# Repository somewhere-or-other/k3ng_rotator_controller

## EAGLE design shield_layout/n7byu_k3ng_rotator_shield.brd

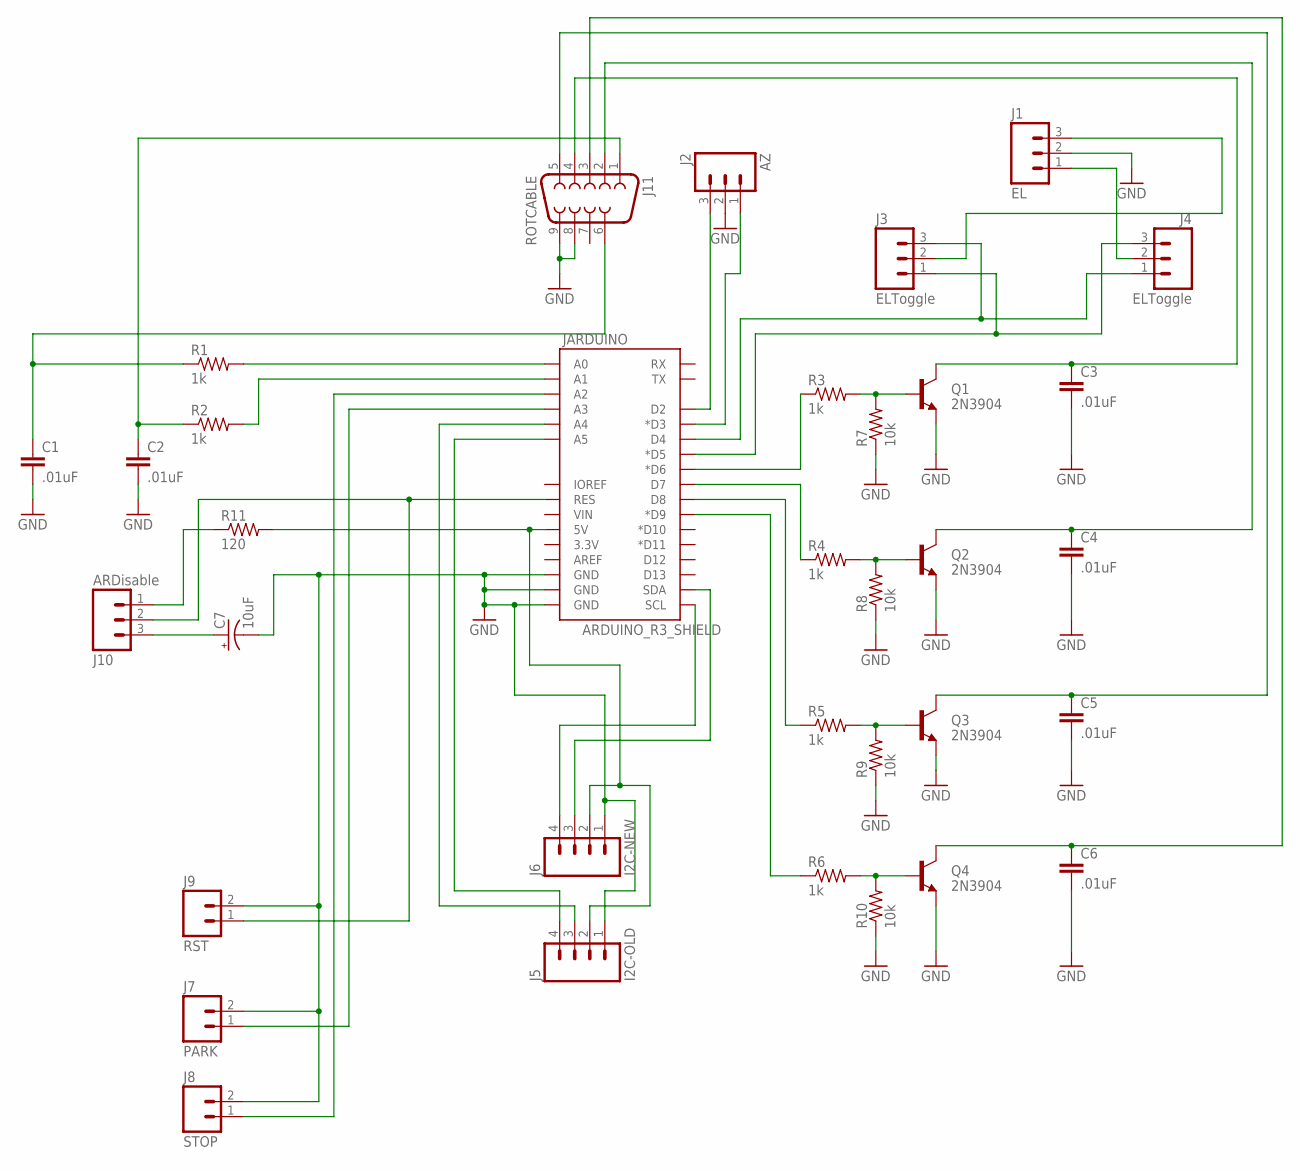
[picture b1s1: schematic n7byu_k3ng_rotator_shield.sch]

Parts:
C1, C2, C3, C4, C5, C6: .01uF; CAP-PTH-SMALLEZ
C7: 10uF; CPOL-RADIAL-100UF-25V
J1: EL; 1X03_LOCK_LONGPADS
J2: AZ; 1X03_LOCK_LONGPADS
J3, J4: ELToggle; 1X03_LOCK_LONGPADS
J5: I2C-OLD; 1X04_LOCK_LONGPADS
J6: I2C-NEW; 1X04_LOCK_LONGPADS
J7: PARK; 1X02_LOCK_LONGPADS
J8: STOP; 1X02_LOCK_LONGPADS
J9: RST; 1X02_LOCK_LONGPADS
J10: ARDisable; 1X03_LOCK_LONGPADS
J11: ROTCABLE; DB9
JARDUINO: ARDUINO_R3_SHIELD; UNO_R3_SHIELD
Q1, Q2, Q3, Q4: 2N3904; TO-92-EZ
R1, R2, R3, R4, R5, R6: 1k; 0204/7
R7, R8, R9, R10: 10k; 0204/7
R11: 120; 0204/7

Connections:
CCW-BUTTON: J2.1, JARDUINO.D3 (*D3)
CW-BUTTON: J2.3, JARDUINO.D2
GND: C1.2, C2.2, C3.2, C4.2, C5.2, C6.2, C7.2 (-), J1.2, J2.2, J5.1, J6.1, J7.2, J8.2, J9.2, J11.8, J11.9, JARDUINO.GND@0 (GND), JARDUINO.GND@1 (GND), JARDUINO.GND@2 (GND), Q1.1 (E), Q2.1 (E), Q3.1 (E), Q4.1 (E), R7.1, R8.1, R9.1, R10.1
unnamed: C1.1, J11.6, R1.1
unnamed: Q1.2 (B), R3.2, R7.2
unnamed: Q2.2 (B), R4.2, R8.2
unnamed: JARDUINO.A0, R1.2
unnamed: C2.1, J11.1, R2.1
unnamed: JARDUINO.A1, R2.2
unnamed: Q3.2 (B), R5.2, R9.2
unnamed: Q4.2 (B), R6.2, R10.2
unnamed: C3.1, J11.4, Q1.3 (C)
unnamed: C4.1, J11.2, Q2.3 (C)
unnamed: C7.1 (+), J10.3
unnamed: C6.1, J11.3, Q4.3 (C)
unnamed: J9.1, J10.2, JARDUINO.RES
unnamed: J1.1, J4.2
unnamed: JARDUINO.D6 (*D6), R3.1
unnamed: JARDUINO.D7, R4.1
unnamed: JARDUINO.D8, R5.1
unnamed: C5.1, J11.5, Q3.3 (C)
unnamed: JARDUINO.D9 (*D9), R6.1
unnamed: J10.1, R11.1
unnamed: J1.3, J3.2
unnamed: J8.1, JARDUINO.A2
unnamed: J3.3, J4.1, JARDUINO.D4
unnamed: J3.1, J4.3, JARDUINO.D5 (*D5)
unnamed: J5.4, JARDUINO.A5
unnamed: J5.2, J6.2, JARDUINO.5V, R11.2
unnamed: J5.3, JARDUINO.A4
unnamed: J7.1, JARDUINO.A3
unnamed: J6.3, JARDUINO.SDA
unnamed: J6.4, JARDUINO.SCL

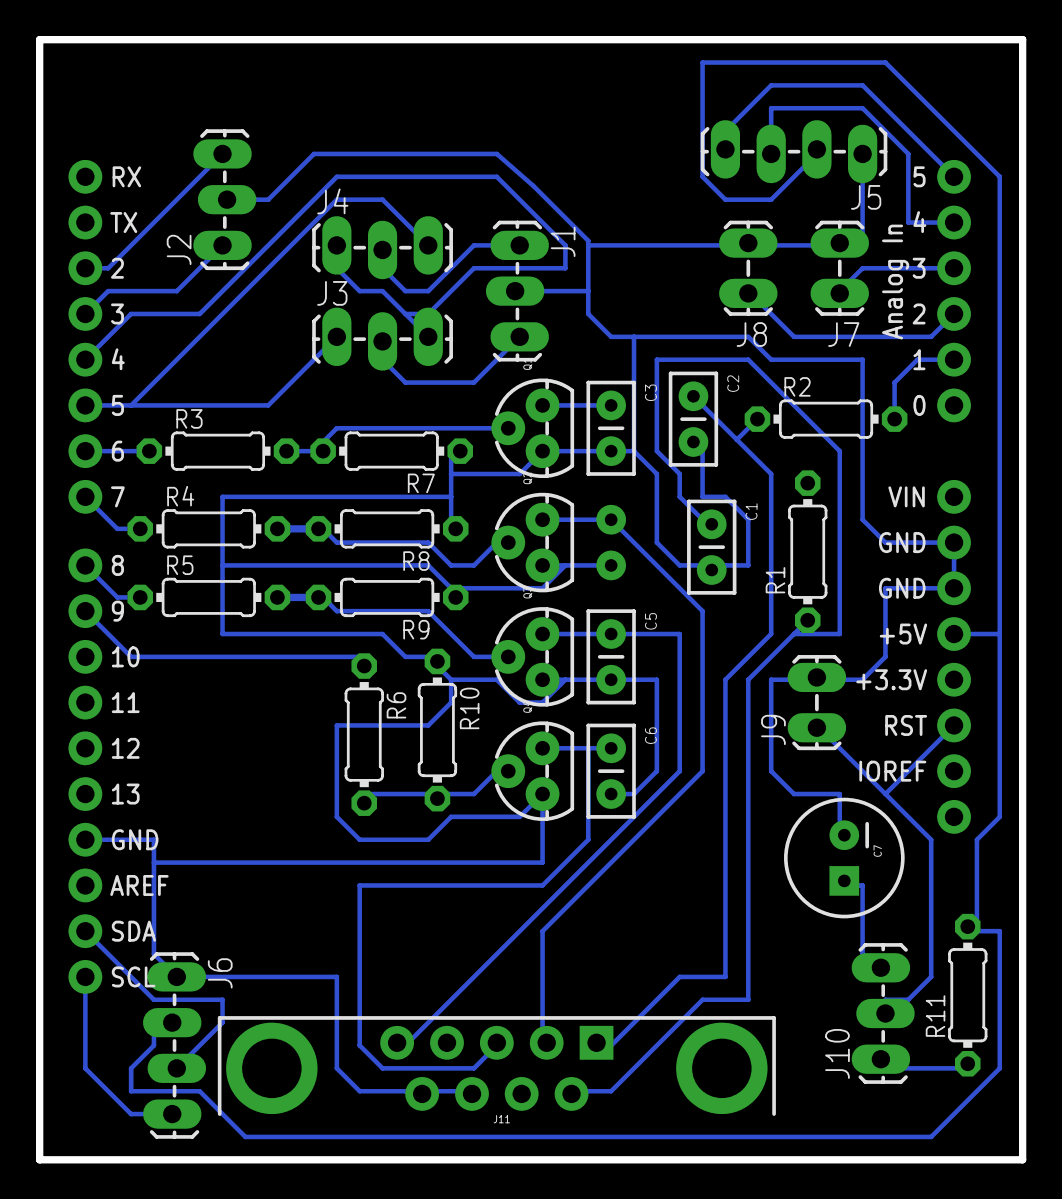
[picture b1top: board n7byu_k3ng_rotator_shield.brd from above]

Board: 2 copper layers, 54.6 x 62.2 mm, 34 parts (1 on the bottom side), 33 nets.

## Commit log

2016-05-04 basic settings for n7byu interface
2016-05-04 first attempt at integrating display. Not sure why it isn't working well.
2016-05-04 clearing out some debug stuff, to keep sketch small enough to fit
2016-05-05 enable button pins, tweak LCD for 20x4
2016-05-05 enable park option
2016-05-11 enable stop & park pins
2016-05-11 enabling general features needed
2016-05-11 enabling display and tweaking format
2016-05-11 assigning pins for various features
2016-05-14 beginning to track eagle layout for shield
2016-05-14 ignoring exterraneous (I think) eagle files
2016-05-15 jumpers for park, stop, reset buttons
2016-05-16 attempt to clear pins D10-D11, to make it compatible with a standard Ethernet shield Still needs testing
2016-05-16 ignoring in-progress board files, too
2016-05-16 converting to 2-row headers to save on space
2016-05-16 begining board layout, using 2 layers; would still like to get down to a single layer if possible
2016-05-17 switching back to separate headers. hopefully will be easier to route on the PCB
2016-05-17 cleaning up schematic file after merge conflict
2016-05-17 another attempt at single-layer routing. not quite there yet
2016-05-17 got it down to 3 jumpers on one layer. still working...
2016-05-18 re-doing with 2-layer PCB, and generating gerbers for seeedstudio (just a test/price check)
2016-05-18 trying to get a smaller (cheaper) board, less than 5x5cm
2016-05-18 actually adding gerber files here.
2016-05-18 adding pulldown resistors, playing with board
2016-05-19 Adding ARDisable headers and 120ohm Resistor, changing all headers to longpads, and tweaking placement
2016-05-19 cleaning up board, renaming components, re-generating Gerber files
2016-05-20 more minor board tweaks, making text easier to read, etc.
2016-05-20 basic board and schematic cleanup, nothing significant
2016-05-20 re-generating gerber files once more
2016-05-22 not sure what the difference is here, or why it needs updated.
2016-05-23 got it to single-side with only 3 jumpers
2016-05-24 down to 2 jumpers on a single-side board
2016-05-24 this one no longer needed
2016-05-24 minor spacing changes
2016-05-25 preparing for BYU EE Shop to etch the single-side board
2016-05-25 manual re-routing to deal with traces touching pads where they shouldn't.
2016-05-25 re-doing with some wider traces and clearences
2016-05-26 regenerating drill files, too
2016-05-26 changed to wider resistor spacing, re-routed traces and re-generated gerbers, etc.
2016-07-06 fixing pin assignment due to apparent cable miswire
2016-07-06 trying to figure out position with N vs S center settings, etc
2016-07-22 changing az settings to avoid flipping n/s center every time
2017-05-08 initial documentation outline
2017-07-04 basic hardware description
2018-01-01 description of hamlib/gpredict setup, azimuth stops & flip-pass, and manual operation
2018-01-02 automatic tracking using gpredict, including snapshots
2018-01-02 including calibration procedure
2018-01-02 filling out references

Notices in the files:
parts and their libraries:
SparkFun-Capacitors: Licensing: Creative Commons ShareAlike 4.0 International - https://creativecommons.org/licenses/by-sa/4.0
